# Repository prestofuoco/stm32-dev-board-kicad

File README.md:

# STM32 dev board [KICAD PCB DESIGN]
This is a 4-layer (sig-gnd-gnd-pwr) STM32F103C8Tx dev board developed in KiCad. 

This design includes SWD, UART, and I2C headers, as well as a USB port.

Published images include a since corrected error in the VBUS ratsnest.

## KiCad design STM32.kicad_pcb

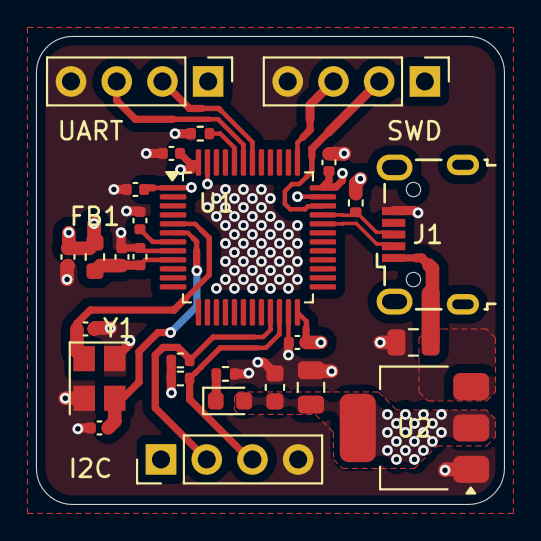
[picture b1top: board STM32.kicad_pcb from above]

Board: 4 copper layers, 26.0 x 26.0 mm, 27 parts (0 on the bottom side), 17 nets.

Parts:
C1, C2, C3, C4, C9: 100n; C_0402_1005Metric
C5: 10u; C_0603_1608Metric
C6: 10n; C_0402_1005Metric
C7, C8: 1u; C_0402_1005Metric
C10, C11: 10p; C_0402_1005Metric
C12, C13: 22u; C_0805_2012Metric
D1: LED; LED_0603_1608Metric
FB1: 120R; L_0603_1608Metric
I2C: Conn_01x04_Pin; PinHeader_1x04_P2.54mm_Vertical
J1: USB_B_Micro; USB_Micro-B_Wuerth_629105150521
R1: 10k; R_0402_1005Metric
R2, R3, R4, R5: 1k5; R_0402_1005Metric
SWD: Conn_01x04_Pin; PinHeader_1x04_P2.54mm_Vertical
U1: STM32F103C8Tx; LQFP-48_7x7mm_P0.5mm
U2: AMS1117-3.3; SOT-223-3_TabPin2
UART: Conn_01x04_Pin; PinHeader_1x04_P2.54mm_Vertical
Y1: Crystal_GND24; Crystal_SMD_3225-4Pin_3.2x2.5mm

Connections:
+3.3V: C1.1, C2.1, C3.1, C4.1, C5.1, C8.1, C13.1, D1.2 (A), FB1.2, I2C.1, R2.2, R4.1, R5.1, SWD.1, U1.1 (VBAT), U1.24 (VDD), U1.36 (VDD), U1.48 (VDD), U2.2 (VO), UART.1
+3.3VA: C6.1, C7.1, FB1.1, U1.9 (VDDA)
/BOOT0: R1.2, U1.44 (BOOT0)
/HSE_IN: C10.1, U1.5 (PD0), Y1.1
/HSE_OUT: C11.1, U1.6 (PD1), Y1.3
/I2C2_SCL: I2C.2, R5.2, U1.21 (PB10)
/I2C2_SDA: I2C.3, R4.2, U1.22 (PB11)
/NRST: C9.1, U1.7 (NRST)
/PWR_LED_K: D1.1 (K), R3.1
/SWCLK: SWD.3, U1.37 (PA14)
/SWDIO: SWD.2, U1.34 (PA13)
/USART1_RX: U1.43 (PB7), UART.3
/USART1_TX: U1.42 (PB6), UART.2
/USB_D+: J1.3 (D+), R2.1, U1.33 (PA12)
/USB_D-: J1.2 (D-), U1.32 (PA11)
GND: C1.2, C2.2, C3.2, C4.2, C5.2, C6.2, C7.2, C8.2, C9.2, C10.2, C11.2, C12.2, C13.2, I2C.4, J1.5 (GND), R1.1, R3.2, SWD.4, U1.8 (VSSA), U1.23 (VSS), U1.35 (VSS), U1.47 (VSS), U2.1 (GND), UART.4, Y1.2, Y1.4
VBUS: C12.1, J1.1 (VBUS), U2.3 (VI)
